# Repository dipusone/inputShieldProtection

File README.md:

# inputShieldProtection
This is shield for the Arduino Nano meant to provide automatic level shifting and DUT protection and the main purpose is to use this in conjunction with the [JTAGENUM](https://github.com/cyphunk/JTAGenum) project.  
The idea and basic are taken from the Input Shield protection found [here](https://github.com/dxa4481/inputProtectionShield),
but it's been updated to use available components.  

As the version from dxa4481 the capabilities are: 
- Input level conversion, including a range from 1.8-5v logic
- Input protection with current limiting and schottky diode array

To use the shield all you have to do is to connect the GND of the arduino to a common ground with the DUT and the REF to the voltage reference of the DUT.
The boards levels the ardiono's pins from 2 to 9 and the pin are marked on the pcb.

# Folder Structure
- **schematics**: contains the Eagle project files
- **exports**: contains the schematics in pdf and the top/bottom of the board
- **boms**: contains the long and short bill of material, the first one is useful during assembly, the second to order the parts

# Short bom

|   Part   |     Value     | Count |       Device       |     Package      |
|----------|---------------|-------|--------------------|------------------|
| IC       | NUP4304MR6T1G |     2 | NUP4304MR6T1G      | SOT95P275X110-6N |
| Mosfet   | BSS138        |     8 | MOSFET-NCHANNELSMD | SOT23-3          |
| Resistor | 1k            |     8 | R-US_R0402         | R0402            |
| Resistor | 10k           |    16 | R-US_R0402         | R0402            |

# Board Layers
| Top Layer                   | Bottom Layer                  |
| :-------------------------: | :-------------------------: |
|    |  |

# Building the board
I've ordered the boards from OSHPARK, you can find the link to the project [here](https://oshpark.com/shared_projects/XDcR2eJg).  
The cost of a single unit should be around 6 euro, but consider that given the shipping cost of the component, 
the fact that oshpark as a minimum order quantity of 3, I ended up building 3 of this.  
For the Reference Voltage connector (REF) I suggest to use right angle strip connector, at least it is working well for me.  

# Testing the board
You can test the board by flashing the Arduino Sketch test_shield.ino in this repository and connecting the REF to the 3.3v of the Arduino.  
The sketch will allow you to cycle the pins and will read the voltage value from the pin A2 , or you can use a multimeter since all the pins are in a HIGH state.

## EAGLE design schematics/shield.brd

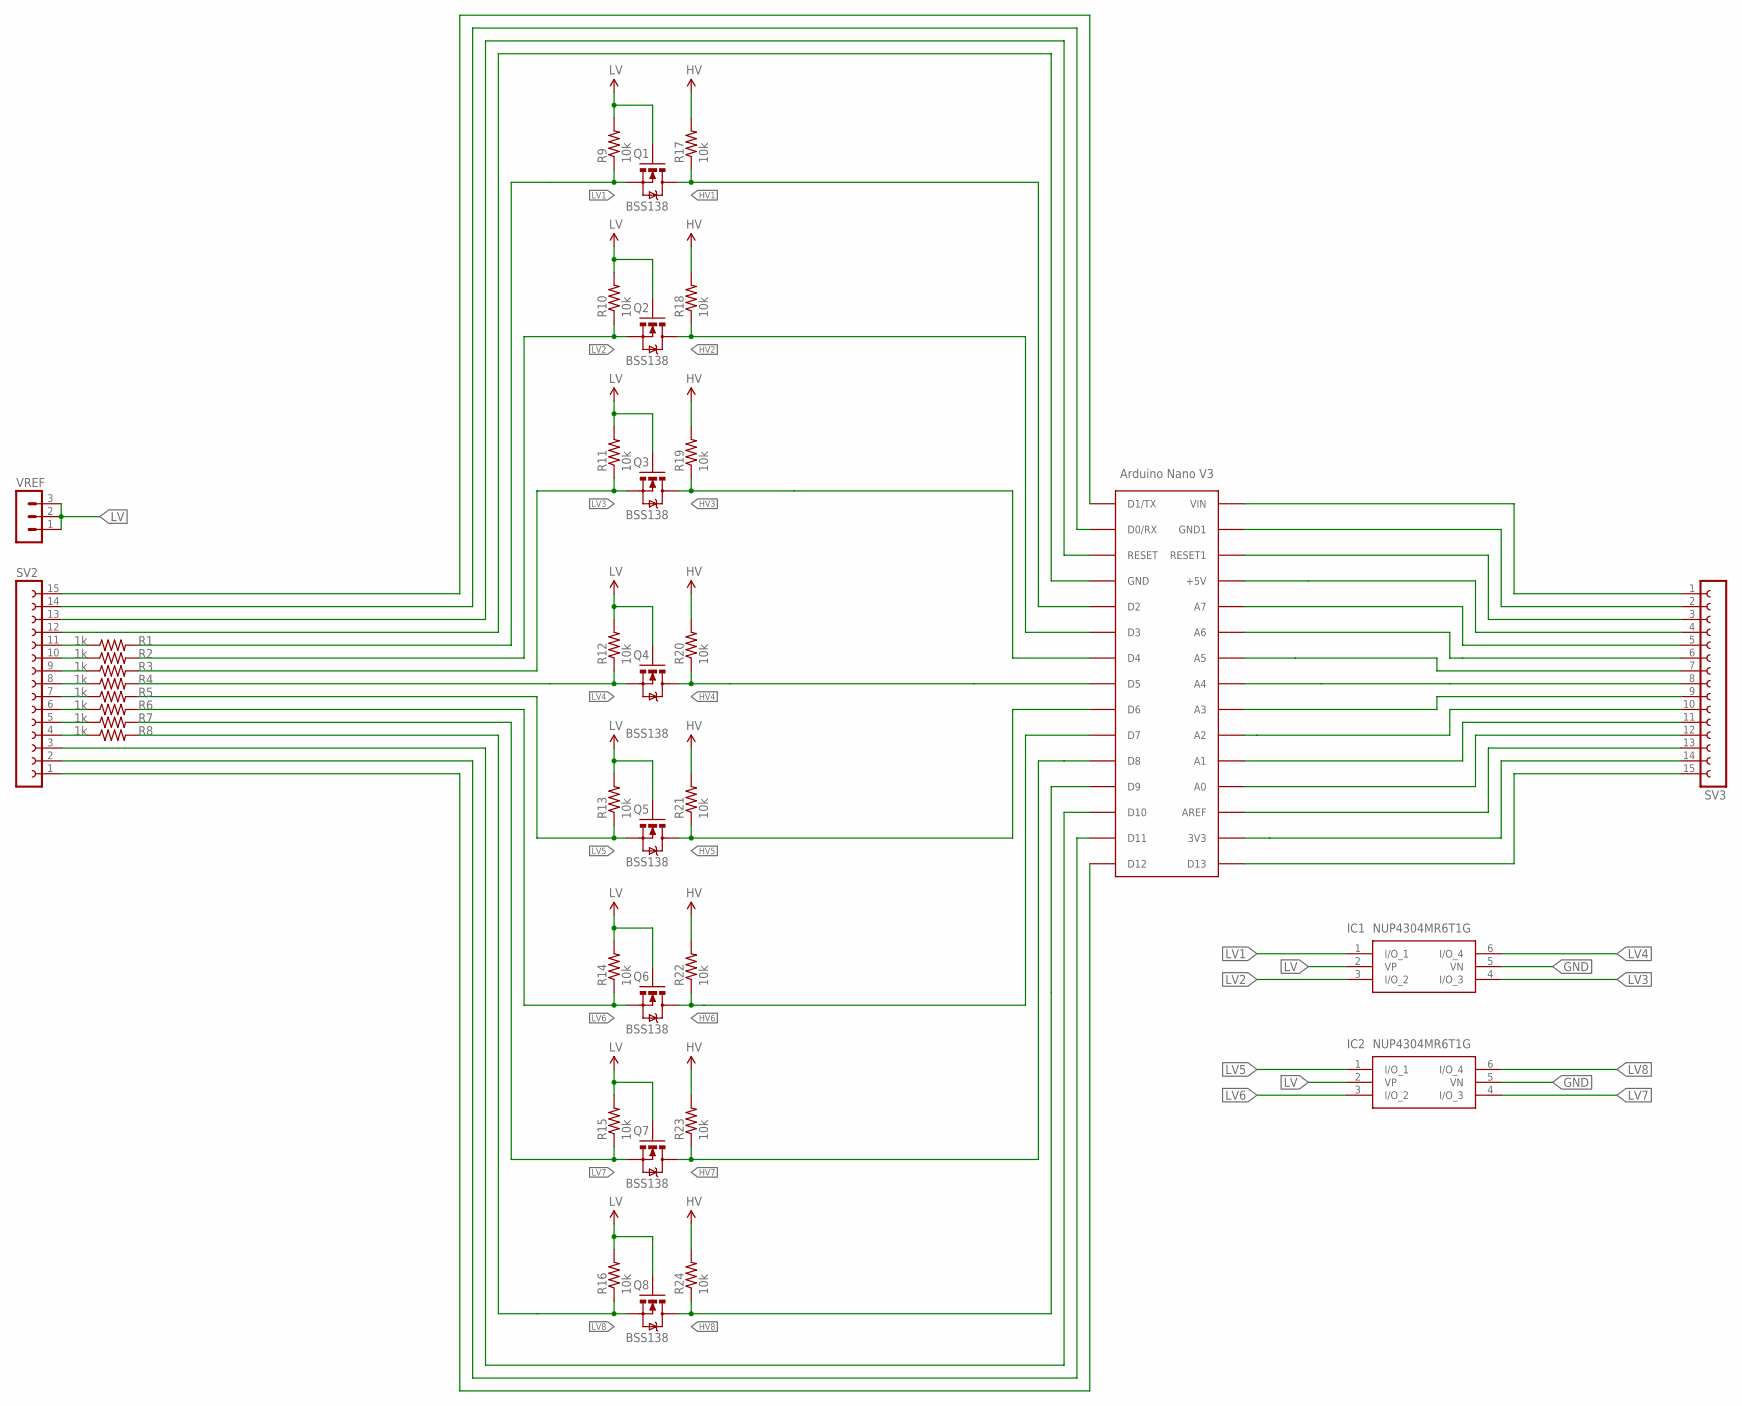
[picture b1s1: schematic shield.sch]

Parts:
IC1, IC2: NUP4304MR6T1G; SOT95P275X110-6N
Q1, Q2, Q3, Q4, Q5, Q6, Q7, Q8: BSS138; SOT23-3
R1, R2, R3, R4, R5, R6, R7, R8: 1k; R0402
R9, R10, R11, R12, R13, R14, R15, R16, R17, R18, R19, R20, R21, R22, R23, R24: 10k; R0402
SV2, SV3: FE15-1; FE15
U1: CRE-LIB1-NL_ARDUINONANO40-MIL-HOLES; ARDUINO-NANO-32-40MIL-HOLES
VREF: MA03-1

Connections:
GND: IC1.5 (VN), IC2.5 (VN), SV2.12, SV3.2, U1.GND, U1.GND1
HV: R17.2, R18.2, R19.2, R20.2, R21.2, R22.2, R23.2, R24.2, SV3.4, U1.+5V
HV1: Q1.3 (D), R17.1, U1.D2
HV2: Q2.3 (D), R18.1, U1.D3
HV3: Q3.3 (D), R19.1, U1.D4
HV4: Q4.3 (D), R20.1, U1.D5
HV5: Q5.3 (D), R21.1, U1.D6
HV6: Q6.3 (D), R22.1, U1.D7
HV7: Q7.3 (D), R23.1, U1.D8
HV8: Q8.3 (D), R24.1, U1.D9
LV: IC1.2 (VP), IC2.2 (VP), Q1.1 (G), Q2.1 (G), Q3.1 (G), Q4.1 (G), Q5.1 (G), Q6.1 (G), Q7.1 (G), Q8.1 (G), R9.2, R10.2, R11.2, R12.2, R13.2, R14.2, R15.2, R16.2, VREF.1, VREF.2, VREF.3
LV1: IC1.1 (I/O_1), Q1.2 (S), R1.2, R9.1
LV2: IC1.3 (I/O_2), Q2.2 (S), R2.2, R10.1
LV3: IC1.4 (I/O_3), Q3.2 (S), R3.2, R11.1
LV4: IC1.6 (I/O_4), Q4.2 (S), R4.2, R12.1
LV5: IC2.1 (I/O_1), Q5.2 (S), R5.2, R13.1
LV6: IC2.3 (I/O_2), Q6.2 (S), R6.2, R14.1
LV7: IC2.4 (I/O_3), Q7.2 (S), R7.2, R15.1
LV8: IC2.6 (I/O_4), Q8.2 (S), R8.2, R16.1
unnamed: SV3.9, U1.A4 (A3)
unnamed: SV3.10, U1.A5 (A2)
unnamed: SV3.11, U1.A6 (A1)
unnamed: SV3.12, U1.A7 (A0)
unnamed: SV3.13, U1.AREF
unnamed: SV3.14, U1.3V3
unnamed: SV3.15, U1.D13
unnamed: SV3.8, U1.A3 (A4)
unnamed: SV3.6, U1.A1 (A6)
unnamed: SV3.5, U1.A0 (A7)
unnamed: SV3.3, U1.RESET1
unnamed: SV3.7, U1.A2 (A5)
unnamed: SV2.15, U1.D1/TX
unnamed: SV2.14, U1.D0/RX
unnamed: SV2.13, U1.RESET
unnamed: SV2.3, U1.D10
unnamed: SV2.2, U1.D11
unnamed: SV2.1, U1.D12
VIN: SV3.1, U1.VIN
_LV1: R1.1, SV2.11
_LV2: R2.1, SV2.10
_LV3: R3.1, SV2.9
_LV4: R4.1, SV2.8
_LV5: R5.1, SV2.7
_LV6: R6.1, SV2.6
_LV7: R7.1, SV2.5
_LV8: R8.1, SV2.4

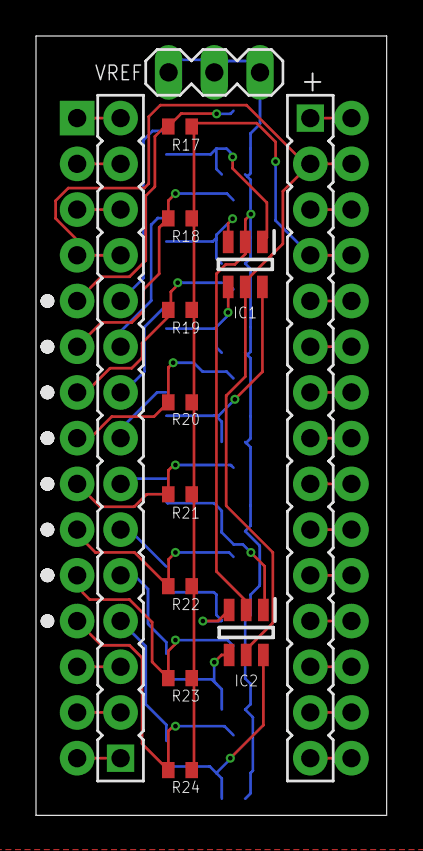
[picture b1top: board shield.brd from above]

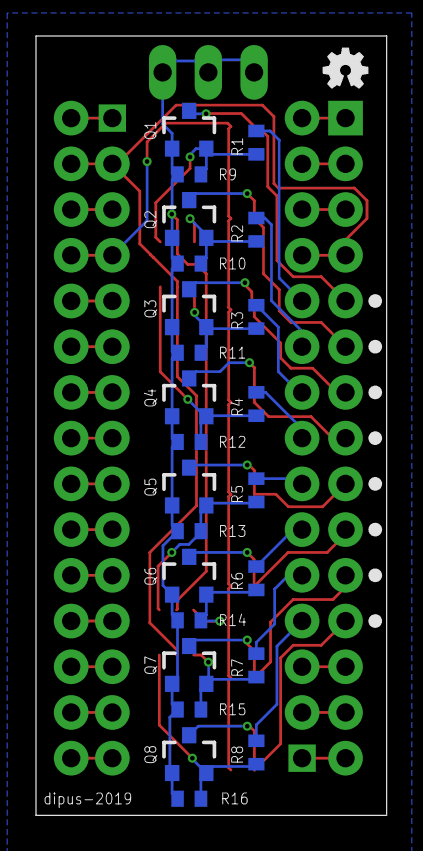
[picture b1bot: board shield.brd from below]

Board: 2 copper layers, 19.5 x 43.3 mm, 39 parts (25 on the bottom side), 46 nets.

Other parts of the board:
U$1: OSHW-LOGO-MINI

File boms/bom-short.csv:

Part,Value,Count,Device,Package
IC,NUP4304MR6T1G,2,NUP4304MR6T1G,SOT95P275X110-6N
Mosfet,BSS138,8,MOSFET-NCHANNELSMD,SOT23-3
Resistor,1k,8,R-US_R0402,R0402
Resistor,10k,16,R-US_R0402,R0402

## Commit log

2019-04-28 Public push

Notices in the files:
parts and their libraries:
SparkFun-Aesthetics: Licensing: Creative Commons ShareAlike 4.0 International - https://creativecommons.org/licenses/by-sa/4.0
